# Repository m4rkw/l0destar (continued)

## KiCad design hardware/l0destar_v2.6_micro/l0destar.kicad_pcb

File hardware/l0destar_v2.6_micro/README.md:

# l0destar v2.6 micro

## Overview

- This is a prototype l0destar vehicle tracker PCB designed to be
  hand-solderable (hot air required)
- It makes use of the [Makerdiary nRF9151 Connect Kit](https://makerdiary.com/products/nrf9151-connectkit) to provide the LTE and GPS
functions
- Component vias are dogleg-routed deliberately in order to keep the PCB costs
as low as possible
- The RF trace width is calculated using a standard 4-layer stackup at JLCPCB,
  different fabrication processes may require adjustment

## Disclaimer

This is a prototype, not a product. Nothing here is validated or certified,
the parts lists are examples rather than a verified BOM, and any test results
recorded below are my own unverified bench observations - repeat the testing
yourself rather than taking them on trust.

**Before building or installing anything from this repository, read the
[full disclaimer](../../DISCLAIMER.md).**

## Test status

| Item | Test | Result | Notes |
|---------|------|--------|-------|
| Input stage | 12V input reverse polarity | PASSED | |
| Input stage | 12V ignition input reverse polarity | PASSED | |
| INA228 | Voltage reading function | PASSED |
| Ignition presence | Ignition sense 3.3v signal | PASSED | |
| LT8609 | 4.2V output | PASSED | |
| Auxillary 3.3V rail | Switches on enable signal | PASSED | |
| Accelerometer | Operates while awake | PASSED | |
| Accelerometer | Wake on motion | PASSED | |
| GPS antenna bias tee | Obtains GPS signal | PASSED | |
| Board | Quiescent current | 120 µA | |

## Features

 - 12V live and 12V ignition inputs with TVS and reverse polarity protection
 - Ignition presence sensing
 - INA228 voltage reading
 - High efficiency buck converter
 - Auxillary 3.3V rail for the GPS antenna bias tee
 - ASM330LHHXG1TR 6-axis IMU gyro/accelerometer
 - USB-C can be connected and disconnected for programming without any power
   disruption

## Changes from v2.5

 - Added stacked 47uF ceramic bulk on the 12V input to provide additional
   resilience against automotive transient spikes

## Power supply

The Connect Kit can be powered through VBUS which would be much simpler as it
can take 5V, but then you have to disconnect the power before connecting a USB
cable. Same for the Nordic dev board - they both explicitly say not to connect
powered USB and VBUS at the same time. Because the intention is to install this
in a vehicle for testing the pragmatic decision was taken to power it with a
4.2V buck feeding the battery connector. With this power connection we can
connect USB-C at any time to update the firmware without needing to disconnect
power.

## Bill of materials

| Item | Description | Specification | Example | Notes |
|------|-------------|---------------|---------|-------|
| MCU | MCU and GSM/GPS 40pin board | nRF9151 Connect Kit | [Makerdiary nRF9151 Connect Kit](https://makerdiary.com/products/nrf9151-connectkit) | |
| S1J1 | Molex Micro-fit 3.0 2x02 PCB connector | 43045-0400 | [43045-0400](https://uk.farnell.com/molex/43045-0400/conn-r-a-pcb-hdr-4pos-2row-3mm/dp/9733019) | | 
| S1J2 | Makerdiary header 1 | 20-pin 2.54mm header | [20-pin pcb header](https://amzn.to/44hTFGN) | |
| S1J3 | Makerdiary header 2 | 20-pin 2.54mm header | [20-pin pcb header](https://amzn.to/44hTFGN) | |
| S1R1 | I2C pull-up resistor | 0402 4.7K 1% | [MP003476](https://uk.farnell.com/multicomp-pro/mp003476/res-4k7-1-0-0625w-0402-thick-film/dp/3392645) | |
| S1R2 | I2C pull-up resistor | 0402 4.7K 1% | [MP003476](https://uk.farnell.com/multicomp-pro/mp003476/res-4k7-1-0-0625w-0402-thick-film/dp/3392645) | |
| S1C1 | 220uF buck output capacitor | 1210 220uF 6.3V 20% X5R | [GRM32ER60J227ME05K](https://uk.farnell.com/murata/grm32er60j227me05k/cap-220-f-6-3v-20-x5r-1210/dp/2671587) | Higher voltage/X7R spec is better if available |
| S1C2 | 220uF buck output capacitor | 1210 220uF 6.3V 20% X5R | [GRM32ER60J227ME05K](https://uk.farnell.com/murata/grm32er60j227me05k/cap-220-f-6-3v-20-x5r-1210/dp/2671587) | Higher voltage/X7R spec is better if available |
| S2Q1 | Reverse-polarity MOSFET | SQ2361 SOT-23 | [SQ2361ES-T1_GE3](https://uk.farnell.com/vishay/sq2361es-t1-ge3/mosfet-aec-q101-p-ch-60v-sot-23/dp/2889711) | |
| S2Q2 | Reverse-polarity MOSFET | SQ2361 SOT-23 | [SQ2361ES-T1_GE3](https://uk.farnell.com/vishay/sq2361es-t1-ge3/mosfet-aec-q101-p-ch-60v-sot-23/dp/2889711) | |
| S2D1 | 15V Zener diode | BZX84C15 | [BZX84C15](https://uk.farnell.com/multicomp-pro/bzx84c15/zener-diode-0-3w-15v-sot-23/dp/2675186) | |
| S2D2 | 400W TVS diode | PTVS33VS1UTR,115 SOD-123W | [PTVS33VS1UTR,115](https://uk.farnell.com/nexperia/ptvs33vs1utr-115/tvs-diode-aecq101-unidir-33v-400w/dp/3440137) | |
| S2D3 | 15V Zener diode | BZX84C15 | [BZX84C15](https://uk.farnell.com/multicomp-pro/bzx84c15/zener-diode-0-3w-15v-sot-23/dp/2675186) | |
| S2D4 | 400W TVS diode | PTVS33VS1UTR,115 SOD-123W | [PTVS33VS1UTR,115](https://uk.farnell.com/nexperia/ptvs33vs1utr-115/tvs-diode-aecq101-unidir-33v-400w/dp/3440137) | |
| S2R1 | Pulldown resistor | 0402 1% 1M | [ERJ2RKF1004X](https://uk.farnell.com/panasonic/erj2rkf1004x/res-1m-1-0-1w-0402-thick-film/dp/2302957) | |
| S2R2 | Pulldown resistor | 0402 1% 1M | [ERJ2RKF1004X](https://uk.farnell.com/panasonic/erj2rkf1004x/res-1m-1-0-1w-0402-thick-film/dp/2302957) | |
| S2C1 | 47uF input capacitor | 2220 >= 50V 20% X7R | [CKG57NX7R1H476M500JH](https://uk.farnell.com/tdk/ckg57nx7r1h476m500jh/cap-stacked-47uf-50v-mlcc-2220/dp/3816888) | |
| S3U1 | INA228 voltage read IC | INA228 10-VSSOP | [INA228](https://www.aliexpress.com/item/1005008704299153.html) | |
| S3C1 | 1uF capacitor | 0402 >= 10V 10% X7R | [KAM05CR71A105KH](https://uk.farnell.com/kyocera-avx/kam05cr71a105kh/capacitor-mlcc-1uf-x7r-10v-0402/dp/4365709) | |
| S3C2 | 100nF capacitor | 0402 >= 25V 10% X7R | [MC0402B104K250CT](https://uk.farnell.com/multicomp-pro/mc0402b104k250ct/cap-0-1-f-25v-10-x7r-0402/dp/2320759) | |
| S4Q1 | Ignition sense MOSFET | 2N7002 SOT-23 | [2N7002](https://uk.farnell.com/multicomp-pro/2n7002/mosfet-n-ch-60v-0-115a-sot-23/dp/4295174) | |
| S4R1 | Ignition sense resistor | 0402 120K 1% | [RC0402FR-07120KL](https://uk.farnell.com/yageo/rc0402fr-07120kl/res-120k-1-0-063w-0402-thick-film/dp/9239480) | |
| S4R2 | Ignition sense resistor | 0402 47K 1% | [ERJ2RKF4702X](https://uk.farnell.com/panasonic/erj2rkf4702x/res-47k-1-0-1w-0402-thick-film/dp/2302806) | |
| S4R3 | Ignition sense resistor | 0402 56K 1% | [MCMR04X5602FTL](https://uk.farnell.com/multicomp-pro/mcmr04x5602ftl/res-56k-1-0-0625w-0402-ceramic/dp/2073131) | |
| S4C1 | 100nF capacitor | 0402 >= 25V 10% X7R | [MC0402B104K250CT](https://uk.farnell.com/multicomp-pro/mc0402b104k250ct/cap-0-1-f-25v-10-x7r-0402/dp/2320759) | |
| S6U1 | Buck converter | LT8609AIMSE MSOP-EP-10 | [LT8609AIMSE#PBF](https://uk.farnell.com/analog-devices/lt8609aimse-pbf/dc-dc-conv-sync-buck-2mhz-125deg/dp/4025049) | |
| S6U2 | Ideal diode | LM66100 | [LM66100](https://www.aliexpress.com/item/1005008565117953.html) | |
| S6L1 | Inductor | XFL4020-222ME | [XFL4020-222MEC](https://uk.farnell.com/coilcraft/xfl4020-222mec/inductor-2-2uh-8a-20-pwr-38mhz/dp/2289216) | |
| S6C1 | 100nF capacitor | 0402 >= 25V 10% X7R | [MC0402B104K250CT](https://uk.farnell.com/multicomp-pro/mc0402b104k250ct/cap-0-1-f-25v-10-x7r-0402/dp/2320759) | |
| S6C2 | 1uF capacitor | 0402 >= 10V 10% X7R | [KAM05CR71A105KH](https://uk.farnell.com/kyocera-avx/kam05cr71a105kh/capacitor-mlcc-1uf-x7r-10v-0402/dp/4365709) | |
| S6C3 | 4.7uF capacitor | 0805 >= 50V 10% X7R | [GRM21BZ71H475KE15K](https://uk.farnell.com/murata/grm21bz71h475ke15k/cap-4-7uf-50v-mlcc-0805/dp/3582887) | |
| S6C4 | 10pF capacitor | 0402 >= 25V 10% X7R | [C0402C100K5RACTU](https://uk.farnell.com/kemet/c0402c100k5ractu/cap-10pf-50v-10-x7r-0402/dp/2821254) | |
| S6C5 | 22uF capacitor | 0805 >= 10V 20% X7T | [GCM21BD71A226MEC4L](https://uk.farnell.com/murata/gcm21bd71a226mec4l/cap-mlcc-22uf-x7t-10v-0805/dp/4813843) | Higher voltage rating/X7R is better if available |
| S6R1 | Oscillator frequency resistor | 0402 18.2K 1% | [RC0402FR-0718K2L](https://uk.farnell.com/yageo/rc0402fr-0718k2l/res-18k2-1-0-0625w-0402-thick/dp/3495542) | 18.2K == 2MHz |
| S6R2 | Output voltage divider resistor | 0402 226K 1% | [MCMR04X2263FTL](https://uk.farnell.com/multicomp-pro/mcmr04x2263ftl/res-226k-1-0-0625w-0402-ceramic/dp/2072796) | VOUT == 0.782V x (1 + S6R3/S6R2) == 4.24V |
| S6R3 | Output voltage divider resistor | 0402 1M 1% | [ERJ2RKF1004X](https://uk.farnell.com/panasonic/erj2rkf1004x/res-1m-1-0-1w-0402-thick-film/dp/2302957) | VOUT == 0.782V x (1 + S6R3/S6R2) == 4.24V |
| S7Q1 | Aux power MOSFET | 2N7002 SOT-23 | [2N7002](https://uk.farnell.com/multicomp-pro/2n7002/mosfet-n-ch-60v-0-115a-sot-23/dp/4295174) | |
| S7Q2 | Aux power MOSFET | DMG3415U SOT-23 | [DMG3415UQ-7](https://uk.farnell.com/diodes-inc/dmg3415uq-7/mosfet-p-ch-20v-4a-sot-23/dp/3943490) | |
| S7R1 | Aux power resistor | 0402 100K 1% | [MCPWR02FTEP1003A](https://uk.farnell.com/multicomp-pro/mcpwr02ftep1003a/res-100k-1-thick-film-0402/dp/4538624) | |
| S7R2 | Aux power resistor | 0402 1M 1% | [ERJ2RKF1004X](https://uk.farnell.com/panasonic/erj2rkf1004x/res-1m-1-0-1w-0402-thick-film/dp/2302957) | |
| S7R3 | Aux power resistor | 0402 100K 1% | [MCPWR02FTEP1003A](https://uk.farnell.com/multicomp-pro/mcpwr02ftep1003a/res-100k-1-thick-film-0402/dp/4538624) | |
| S7R4 | Aux power resistor | 0402 470K 1% | [ERJ2RKF4703X](https://uk.farnell.com/panasonic/erj2rkf4703x/res-470k-1-0-1w-0402-thick-film/dp/2302916) | |
| S8U1 | ASM330LHHXTR accelerometer | ASM330LHHXTR | [ASM330LHHXTR](https://estore.st.com/en/products/mems-and-sensors/inemo-inertial-modules/asm330lhhx.html) | |
| S8C1 | 100nF capacitor | 0402 >= 25V 10% X7R | [MC0402B104K250CT](https://uk.farnell.com/multicomp-pro/mc0402b104k250ct/cap-0-1-f-25v-10-x7r-0402/dp/2320759) | |
| S8C2 | 10uF capacitor | 0603 >= 6.3V 20% X7T | [GRT188D71A106ME13D](https://uk.farnell.com/murata/grt188d71a106me13d/cap-mlcc-10uf-x7t-10v-0603/dp/4335734) | Higher voltage/X7R is better if available |
| S8C3 | 100nF capacitor | 0402 >= 25V 10% X7R | [MC0402B104K250CT](https://uk.farnell.com/multicomp-pro/mc0402b104k250ct/cap-0-1-f-25v-10-x7r-0402/dp/2320759) | |
| S13R1 | LED resistor | 0402 1K 1% | [CRCW04021K00FKED](https://uk.farnell.com/vishay/crcw04021k00fked/res-1k-1-0-063w-0402-thick-film/dp/1469662) | |
| S13R2 | LED resistor | 0402 1K 1% | [CRCW04021K00FKED](https://uk.farnell.com/vishay/crcw04021k00fked/res-1k-1-0-063w-0402-thick-film/dp/1469662) | |
| S13R3 | LED resistor | 0402 1K 1% | [CRCW04021K00FKED](https://uk.farnell.com/vishay/crcw04021k00fked/res-1k-1-0-063w-0402-thick-film/dp/1469662) | |
| S13D1 | Status LED | 0603 | [MP001249](https://uk.farnell.com/multicomp-pro/mp001249/led-red-385mcd-629nm-0603/dp/3265380) | |
| S13D2 | Status LED | 0603 | [MP001249](https://uk.farnell.com/multicomp-pro/mp001249/led-red-385mcd-629nm-0603/dp/3265380) | |
| S13D3 | Status LED | 0603 | [MP001249](https://uk.farnell.com/multicomp-pro/mp001249/led-red-385mcd-629nm-0603/dp/3265380) | |
| S15J1 | u.FL PCB connector | 50 ohm | [U.FL-R-SMT(01)](https://uk.farnell.com/hirose-hrs/u-fl-r-smt-01/rf-coaxial-u-fl-straight-jack/dp/3908021) | |
| S15J2 | SMA PCB connector | 50 ohm | [SMA-J-P-H-RA-TH1](https://uk.farnell.com/samtec/sma-j-p-h-ra-th1/rf-coaxial-sma-jack-50-ohm-pcb/dp/2856817) | |
| S15J3 | u.FL PCB connector | 50 ohm | [U.FL-R-SMT(01)](https://uk.farnell.com/hirose-hrs/u-fl-r-smt-01/rf-coaxial-u-fl-straight-jack/dp/3908021) | |
| S15J4 | SMA PCB connector | 50 ohm | [SMA-J-P-H-RA-TH1](https://uk.farnell.com/samtec/sma-j-p-h-ra-th1/rf-coaxial-sma-jack-50-ohm-pcb/dp/2856817) | |
| S15U1 | Ideal diode | LM66100 | [LM66100](https://www.aliexpress.com/item/1005008565117953.html) | |
| S15FB1 | Ferrite bead | 600 ohm | [BLM15PX601SZ1D](https://uk.farnell.com/murata/blm15px601sz1d/ferrite-bead-0-9a-0-23ohm-0402/dp/3678458) | |
| S15L1 | RF inductor | 0603 47-100 nH, SRF > 2GHz | [LQW18AN68NJ00D](https://uk.farnell.com/murata/lqw18an68nj00d/inductor-68nh-2-2ghz-0-34a-0603/dp/3471533) | |
| S15C1 | 100pF RF capacitor | 0402 >= 25V 1% C0G / NP0 | [AC0402FRNPO9BN101](https://uk.farnell.com/yageo/ac0402frnpo9bn101/cap-100pf-50v-mlcc-0402/dp/4166091) | |
| S15C2 | 100pF RF capacitor | 0402 >= 25V 1% C0G / NP0 | [AC0402FRNPO9BN101](https://uk.farnell.com/yageo/ac0402frnpo9bn101/cap-100pf-50v-mlcc-0402/dp/4166091) | |
| S15C3 | 10nF RF capacitor | 0402 >= 25V 5% C0G / NP0 | [GRM1555CYA103JE01D](https://uk.farnell.com/murata/grm1555cya103je01d/cap-mlcc-0-01uf-c0g-np0-35v-0402/dp/4792250) | |
| S15C4 | 1uF RF capacitor | 0402 >= 25V 10% X7R | [KAM05CR71A105KH](https://uk.farnell.com/kyocera-avx/kam05cr71a105kh/capacitor-mlcc-1uf-x7r-10v-0402/dp/4365709) | |
| - | u.FL cable - LTE | 50 ohm 35mm | [U.FL-2LPHF6-04N1TV-A-35](https://uk.farnell.com/hirose-hrs/u-fl-2lphf6-04n1tv-a-35/cbl-assy-u-fl-r-a-plug-r-a-plug/dp/4294251) | |
| - | u.FL cable - GPS | 50 ohm 35mm | [U.FL-2LPHF6-04N1TV-A-35](https://uk.farnell.com/hirose-hrs/u-fl-2lphf6-04n1tv-a-35/cbl-assy-u-fl-r-a-plug-r-a-plug/dp/4294251) | |
| - | JST power cable | Ultra-thin MX1.25 51146 | [10PCS MX1.25 51146 Cable](https://www.aliexpress.com/item/4000586964114.html) | |

## Parts list

| Item | Quantity | Specification | Example | Notes |
|------|----------|---------------|---------|-------|
| MCU and GSM/GPS 40pin board | 1 | nRF9151 Connect Kit | [Makerdiary nRF9151 Connect Kit](https://makerdiary.com/products/nrf9151-connectkit) | |
| Molex Micro-fit 3.0 2x02 PCB connector | 1 | 43045-0400 | [43045-0400](https://uk.farnell.com/molex/43045-0400/conn-r-a-pcb-hdr-4pos-2row-3mm/dp/9733019) | | 
| 20pin header | 2 | 20-pin 2.54mm header | [20-pin pcb header](https://amzn.to/44hTFGN) | |
| 1K 0402 resistor | 3 | 0402 1K 1% | [CRCW04021K00FKED](https://uk.farnell.com/vishay/crcw04021k00fked/res-1k-1-0-063w-0402-thick-film/dp/1469662) | |
| 4.7K 0402 resistor | 2 | 0402 4.7K 1% | [MP003476](https://uk.farnell.com/multicomp-pro/mp003476/res-4k7-1-0-0625w-0402-thick-film/dp/3392645) | |
| 18.2K 0402 resistor | 1 | 0402 18.2K 1% | [RC0402FR-0718K2L](https://uk.farnell.com/yageo/rc0402fr-0718k2l/res-18k2-1-0-0625w-0402-thick/dp/3495542) | 18.2K == 2MHz |
| 47K 0402 resistor | 1 | 0402 47K 1% | [ERJ2RKF4702X](https://uk.farnell.com/panasonic/erj2rkf4702x/res-47k-1-0-1w-0402-thick-film/dp/2302806) | |
| 56K 0402 resistor | 1 | 0402 56K 1% | [MCMR04X5602FTL](https://uk.farnell.com/multicomp-pro/mcmr04x5602ftl/res-56k-1-0-0625w-0402-ceramic/dp/2073131) | |
| 100K 0402 resistor | 2 | 0402 100K 1% | [MCPWR02FTEP1003A](https://uk.farnell.com/multicomp-pro/mcpwr02ftep1003a/res-100k-1-thick-film-0402/dp/4538624) | |
| 120K 0402 resistor | 1 | 0402 120K 1% | [RC0402FR-07120KL](https://uk.farnell.com/yageo/rc0402fr-07120kl/res-120k-1-0-063w-0402-thick-film/dp/9239480) | |
| 226K 0402 resistor | 1 | 0402 226K 1% | [MCMR04X2263FTL](https://uk.farnell.com/multicomp-pro/mcmr04x2263ftl/res-226k-1-0-0625w-0402-ceramic/dp/2072796) | VOUT == 0.782V x (1 + S6R3/S6R2) == 4.24V |
| 470K 0402 resistor | 1 | 0402 470K 1% | [ERJ2RKF4703X](https://uk.farnell.com/panasonic/erj2rkf4703x/res-470k-1-0-1w-0402-thick-film/dp/2302916) | |
| 1M 0402 resistor | 4 | 0402 1M 1% | [ERJ2RKF1004X](https://uk.farnell.com/panasonic/erj2rkf1004x/res-1m-1-0-1w-0402-thick-film/dp/2302957) | |
| 10pF 0402 capacitor | 1 | 0402 >= 25V 10% X7R | [C0402C100K5RACTU](https://uk.farnell.com/kemet/c0402c100k5ractu/cap-10pf-50v-10-x7r-0402/dp/2821254) | |
| 100pF 0402 RF capacitor | 2 | 0402 >= 25V 1% C0G / NP0 | [AC0402FRNPO9BN101](https://uk.farnell.com/yageo/ac0402frnpo9bn101/cap-100pf-50v-mlcc-0402/dp/4166091) | |
| 10nF 0402 RF capacitor | 1 | 0402 >= 25V 5% C0G / NP0 | [GRM1555CYA103JE01D](https://uk.farnell.com/murata/grm1555cya103je01d/cap-mlcc-0-01uf-c0g-np0-35v-0402/dp/4792250) | |
| 100nF 0402 capacitor | 5 | 0402 >= 25V 10% X7R | [MC0402B104K250CT](https://uk.farnell.com/multicomp-pro/mc0402b104k250ct/cap-0-1-f-25v-10-x7r-0402/dp/2320759) | |
| 1uF 0402 capacitor | 3 | 0402 >= 10V 10% X7R | [KAM05CR71A105KH](https://uk.farnell.com/kyocera-avx/kam05cr71a105kh/capacitor-mlcc-1uf-x7r-10v-0402/dp/4365709) | |
| 4.7uF 0805 capacitor | 1 | 0805 >= 50V 10% X7R | [GRM21BZ71H475KE15K](https://uk.farnell.com/murata/grm21bz71h475ke15k/cap-4-7uf-50v-mlcc-0805/dp/3582887) | |
| 10uF 0603 capacitor | 1 | 0603 >= 6.3V 20% X7T | [GRT188D71A106ME13D](https://uk.farnell.com/murata/grt188d71a106me13d/cap-mlcc-10uf-x7t-10v-0603/dp/4335734) | Higher voltage/X7R is better if available |
| 22uF 0805 capacitor | 1 | 0805 >= 10V 20% X7T | [GCM21BD71A226MEC4L](https://uk.farnell.com/murata/gcm21bd71a226mec4l/cap-mlcc-22uf-x7t-10v-0805/dp/4813843) | Higher voltage rating/X7R is better if available |
| 47uF 2220 capacitor | 1 | 2220 >= 50V 20% X7R | [CKG57NX7R1H476M500JH](https://uk.farnell.com/tdk/ckg57nx7r1h476m500jh/cap-stacked-47uf-50v-mlcc-2220/dp/3816888) | |
| 220uF 1210 capacitor | 2 | 1210 6.3V 20% X5R | [GRM32ER60J227ME05K](https://uk.farnell.com/murata/grm32er60j227me05k/cap-220-f-6-3v-20-x5r-1210/dp/2671587) | Higher voltage/X7R spec is better if available |
| MOSFET | 2 | SQ2361 SOT-23 | [SQ2361ES-T1_GE3](https://uk.farnell.com/vishay/sq2361es-t1-ge3/mosfet-aec-q101-p-ch-60v-sot-23/dp/2889711) | |
| MOSFET | 2 | 2N7002 SOT-23 | [2N7002](https://uk.farnell.com/multicomp-pro/2n7002/mosfet-n-ch-60v-0-115a-sot-23/dp/4295174) | |
| MOSFET | 1 | DMG3415U SOT-23 | [DMG3415UQ-7](https://uk.farnell.com/diodes-inc/dmg3415uq-7/mosfet-p-ch-20v-4a-sot-23/dp/3943490) | |
| 15V Zener diode | 2 | BZX84C15 | [BZX84C15](https://uk.farnell.com/multicomp-pro/bzx84c15/zener-diode-0-3w-15v-sot-23/dp/2675186) | |
| 400W TVS diode | 2 | PTVS33VS1UTR,115 SOD-123W | [PTVS33VS1UTR,115](https://uk.farnell.com/nexperia/ptvs33vs1utr-115/tvs-diode-aecq101-unidir-33v-400w/dp/3440137) | |
| Ideal diode | 2 | LM66100 | [LM66100](https://www.aliexpress.com/item/1005008565117953.html) | |
| INA228 voltage read IC | 1 | INA228 10-VSSOP | [INA228](https://www.aliexpress.com/item/1005008704299153.html) | |
| Buck converter | 1 | LT8609AIMSE MSOP-EP-10 | [LT8609AIMSE#PBF](https://uk.farnell.com/analog-devices/lt8609aimse-pbf/dc-dc-conv-sync-buck-2mhz-125deg/dp/4025049) | |
| Inductor | 1 | XFL4020-222ME | [XFL4020-222MEC](https://uk.farnell.com/coilcraft/xfl4020-222mec/inductor-2-2uh-8a-20-pwr-38mhz/dp/2289216) | |
| ASM330LHHXTR accelerometer | 1 | ASM330LHHXTR | [ASM330LHHXTR](https://estore.st.com/en/products/mems-and-sensors/inemo-inertial-modules/asm330lhhx.html) | |
| 0603 LED | 3 | 0603 | [MP001249](https://uk.farnell.com/multicomp-pro/mp001249/led-red-385mcd-629nm-0603/dp/3265380) | |
| Ferrite bead | 1 | 600 ohm | [BLM15PX601SZ1D](https://uk.farnell.com/murata/blm15px601sz1d/ferrite-bead-0-9a-0-23ohm-0402/dp/3678458) | |
| RF inductor | 1 | 0603 47-100 nH, SRF > 2GHz | [LQW18AN68NJ00D](https://uk.farnell.com/murata/lqw18an68nj00d/inductor-68nh-2-2ghz-0-34a-0603/dp/3471533) | |
| u.FL PCB connector | 2 | 50 ohm | [U.FL-R-SMT(01)](https://uk.farnell.com/hirose-hrs/u-fl-r-smt-01/rf-coaxial-u-fl-straight-jack/dp/3908021) | |
| SMA PCB connector | 2 | 50 ohm | [SMA-J-P-H-RA-TH1](https://uk.farnell.com/samtec/sma-j-p-h-ra-th1/rf-coaxial-sma-jack-50-ohm-pcb/dp/2856817) | |
| u.FL cable - GPS | 2 | 50 ohm 35mm | [U.FL-2LPHF6-04N1TV-A-35](https://uk.farnell.com/hirose-hrs/u-fl-2lphf6-04n1tv-a-35/cbl-assy-u-fl-r-a-plug-r-a-plug/dp/4294251) | |
| JST power cable | 1 | Ultra-thin MX1.25 51146 | [10PCS MX1.25 51146 Cable](https://www.aliexpress.com/item/4000586964114.html) | |

## Images

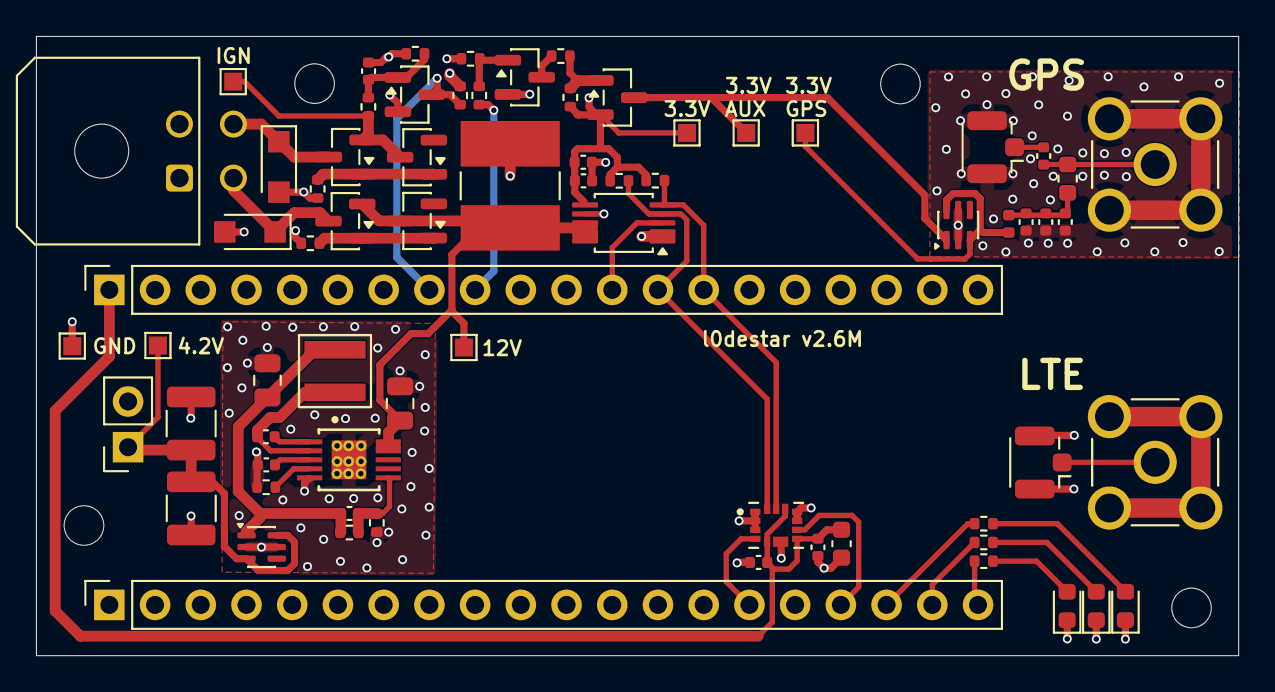
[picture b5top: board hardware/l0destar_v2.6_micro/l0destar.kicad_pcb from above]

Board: 4 copper layers, 66.8 x 34.4 mm, 74 parts (0 on the bottom side), 38 nets.

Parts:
GND1: TestPoint; TestPoint_Pad_1.0x1.0mm
H1, H2, H3, H4: MountingHole; MountingHole_2.2mm_M2
PP3V3, PP3V3AUX1, PP3V3GPS2, PP4V5, PP12VIP1, PP12VP1: TestPoint; TestPoint_Pad_1.0x1.0mm
S1C1, S1C2: 220uF; C_1210_3225Metric
S1J1: Main connector; Molex_Micro-Fit_3.0_43045-0400_2x02_P3.00mm_Horizontal
S1J2: Conn_01x20_Socket; MakerDiary_nRF9151_ConnectKit_PinHeader_1-20
S1J3: Conn_01x20_Socket_21-40; MakerDiary_nRF9151_ConnectKit_PinHeader_21-40
S1J4: VCC; PinSocket_1x02_P2.54mm_Vertical
S1R1, S1R2: 4.7K; R_0402_1005Metric
S2C1: CKG57NX7R1H476M500JH 47uF; CAPC6050X550N
S2D1, S2D3: BZX84C15; SOT-23
S2D2, S2D4: PTVS33VS1UTR,115; Nexperia_CFP3_SOD-123W
S2Q1, S2Q2: SQ2361; SOT-23
S2R1, S2R2, S6R3, S7R2: 1M; R_0402_1005Metric
S3C1, S6C2, S15C4: 1uF; C_0402_1005Metric
S3C2, S4C1, S6C1, S8C1, S8C3: 100nF; C_0402_1005Metric
S3U1: INA228; TSSOP-10_3x3mm_P0.5mm
S4Q1, S7Q1: 2N7002; SOT-23
S4R1: 120K; R_0402_1005Metric
S4R2: 47K; R_0402_1005Metric
S4R3: 56K; R_0402_1005Metric
S6C3: 4.7uF; C_0805_2012Metric
S6C4: 10pF; C_0402_1005Metric
S6C5: 22uF; C_0805_2012Metric
S6L1: XFL4020-222ME; IND_XFL4020-222ME
S6R1: 18.2K; R_0402_1005Metric
S6R2: 226K; R_0402_1005Metric
S6U1: LT8609AIMSE_PBF; LT8609AIMSE_WITH_GROUND_VIAS
S6U2, S15U1: LM66100DCK; SOT-363_SC-70-6
S7Q2: DMG3415U; SOT-23
S7R1, S7R3: 100K; R_0402_1005Metric
S7R4: 470K; R_0402_1005Metric
S8C2: 10uF; C_0603_1608Metric
S8U1: ASM330LHHXTR; XDCR_ASM330LHHXTR
S13D1, S13D2, S13D3: LED; LED_0603_1608Metric
S13R1, S13R2, S13R3: 1K; R_0402_1005Metric
S15C1, S15C2: 100pF; C_0402_1005Metric
S15C3: 10nF; C_0402_1005Metric
S15FB1: 600R; L_0402_1005Metric
S15J1: GPS_UFL; U.FL_Hirose_U.FL-R-SMT-1_Vertical
S15J2: GPS_SMA; SAMTEC_SMA-J-P-H-RA-TH1
S15J3: GSM_UFL; U.FL_Hirose_U.FL-R-SMT-1_Vertical
S15J4: GSM_SMA; SAMTEC_SMA-J-P-H-RA-TH1
S15L1: 47-100 nH, SRF > 2 GHz; L_0603_1608Metric

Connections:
ACCELL_INT1: S1J2.15, S8U1.4 (INT1)
ACCELL_INT2: S1J2.17, S8U1.9 (INT2)
AUX_ENABLE: S1J3.32 (Pin_9), S7R1.1
GND: GND1.1 (1_1), S1C1.2, S1C2.2, S1J1.1, S1J2.3 (GND), S1J3.39 (Pin_2), S1J4.2, S2C1.2, S2D2.2 (A), S2D4.2 (A), S2R1.2, S2R2.2, S3C1.1, S3C2.1, S3U1.1 (A1), S3U1.2 (A0), S3U1.7 (GND), S4C1.2, S4Q1.2 (S), S4R2.1, S6C2.2, S6C3.2, S6C5.2, S6R1.2, S6R2.2, S6U1.5 (SYNC), S6U1.11 (GND), S6U2.2 (GND), S6U2.5 (ST), S7Q1.2 (S), S7R2.1, S8C1.2, S8C2.2, S8C3.2, S8U1.1 (SDO/SA0), S8U1.2 (MSDA), S8U1.3 (MSCL), S8U1.6 (NC), S8U1.7 (GND), S8U1.10 (NC), S8U1.11 (NC), S13D1.1 (K), S13D2.1 (K), S13D3.1 (K), S15C2.2, S15C3.2, S15C4.2, S15J1.2 (Ext), S15J2.2, S15J2.3, S15J2.4, S15J2.5, S15J3.2 (Ext), S15J4.2, S15J4.3, S15J4.4, S15J4.5, S15U1.2 (GND), S15U1.5 (ST)
I2C_SCL: S1J3.27 (Pin_14), S1R2.1, S3U1.5 (SCL), S8U1.13 (SCL)
I2C_SDA: S1J3.28 (Pin_13), S1R1.1, S3U1.4 (SDA), S8U1.14 (SDA)
IGN_SENSE: S1J3.33 (Pin_8), S4Q1.3 (D), S4R3.2
INA_ALRT: S1J3.29 (Pin_12), S3U1.3 (~Alert)
LED1: S1J2.20, S13R1.2
LED2: S1J2.19, S13R2.2
LED3: S1J2.18, S13R3.2
unnamed: S2D1.1 (A), S2Q1.1 (G), S2R1.1
unnamed: S2D3.1 (A), S2Q2.1 (G), S2R2.1
unnamed: S4C1.1, S4Q1.1 (G), S4R1.2, S4R2.2
unnamed: S6C1.1, S6U1.1 (BST)
unnamed: S6C4.1, S6R2.1, S6R3.1, S6U1.6 (FB)
unnamed: S6C2.1, S6U1.3 (INTVCC)
unnamed: S6R1.1, S6U1.4 (RT)
unnamed: S6C1.2, S6L1.1, S6U1.2 (SW)
unnamed: S6C4.2, S6C5.1, S6L1.2, S6R3.2, S6U2.1 (VIN)
unnamed: S7Q1.3 (D), S7R3.2
unnamed: S7Q1.1 (G), S7R1.2, S7R2.2
unnamed: S7Q2.1 (G), S7R3.1, S7R4.2
unnamed: S13D1.2 (A), S13R1.1
unnamed: S13D2.2 (A), S13R2.1
unnamed: S13D3.2 (A), S13R3.1
unnamed: S15C2.1, S15C3.1, S15C4.1, S15FB1.2, S15L1.1
unnamed: S15C1.1, S15J1.1 (In)
unnamed: S15J3.1 (In), S15J4.1
PP3V3: PP3V3.1 (1_1), S1J3.40 (Pin_1), S1R1.2, S1R2.2, S3C1.2, S3C2.2, S3U1.6 (VS), S4R3.1, S7Q2.2 (S), S7R4.1, S8C1.1, S8C2.1, S8C3.1, S8U1.5 (VDD_IO), S8U1.8 (VDD), S8U1.12 (CS)
PP3V3_AUX: PP3V3AUX1.1 (1_1), S7Q2.3 (D), S15U1.1 (VIN)
PP3V3_GPS: PP3V3GPS2.1 (1_1), S15FB1.1, S15U1.3 (~CE), S15U1.6 (VOUT)
PP4V2: PP4V5.1 (1_1), S1C1.1, S1C2.1, S1J4.1, S6U2.3 (~CE), S6U2.6 (VOUT)
PP12V: S1J1.3, S2D4.1 (K), S2Q2.3 (D)
PP12VI: S1J1.4, S2D2.1 (K), S2Q1.3 (D)
PP12VIP: PP12VIP1.1 (1_1), S2D1.3 (K), S2Q1.2 (S), S4R1.1
PP12VP: PP12VP1.1 (1_1), S2C1.1, S2D3.3 (K), S2Q2.2 (S), S3U1.8 (Vbus), S3U1.9 (Vin-), S3U1.10 (Vin+), S6C3.1, S6U1.9 (VIN), S6U1.10 (EN/UV)
RF: S15C1.2, S15J2.1, S15L1.2

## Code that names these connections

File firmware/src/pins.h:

#ifndef PINS_H_
#define PINS_H_

/* PCB pin assignments — P0.x GPIO numbers, -1 = not fitted on this board.
 *
 * All values come from Kconfig (APP_PIN_*).  The per-board defaults live in
 * Kconfig.boards, selected by the APP_BOARD choice; a bench or board variant
 * can still remap any signal from local.conf without touching code. */
#define PIN_K1_TX      CONFIG_APP_PIN_K1_TX
#define PIN_K1_RX      CONFIG_APP_PIN_K1_RX
#define PIN_K2_TX      CONFIG_APP_PIN_K2_TX
#define PIN_K2_RX      CONFIG_APP_PIN_K2_RX
#define PIN_L_SEND     CONFIG_APP_PIN_L_SEND
#define PIN_L_RECV     CONFIG_APP_PIN_L_RECV
#define PIN_L_SENSE    CONFIG_APP_PIN_L_SENSE
#define PIN_K_EN       CONFIG_APP_PIN_K_EN
#define PIN_K_SLEEP    CONFIG_APP_PIN_K_SLEEP
#define PIN_AUX_SW     CONFIG_APP_PIN_AUX_SW
#define PIN_OBD_EN     CONFIG_APP_PIN_OBD_EN
#define PIN_CAN_EN     CONFIG_APP_PIN_CAN_EN
#define PIN_TWI_SDA    CONFIG_APP_PIN_TWI_SDA
#define PIN_TWI_SCL    CONFIG_APP_PIN_TWI_SCL
#define PIN_INA_ALRT   CONFIG_APP_PIN_INA_ALRT
#define PIN_ACC_INT1   CONFIG_APP_PIN_ACC_INT1
#define PIN_ACC_INT2   CONFIG_APP_PIN_ACC_INT2
#define PIN_IGN_SENSE  CONFIG_APP_PIN_IGN_SENSE

/* MCP2518FD CAN controller (SPI bit-banged; -1 on boards without CAN) */
#define PIN_CAN_SCK    CONFIG_APP_PIN_CAN_SCK
#define PIN_CAN_SDI    CONFIG_APP_PIN_CAN_SDI
#define PIN_CAN_SDO    CONFIG_APP_PIN_CAN_SDO
#define PIN_CAN_CS     CONFIG_APP_PIN_CAN_CS
#define PIN_CAN_INT    CONFIG_APP_PIN_CAN_INT

/* Status LEDs (-1 = not fitted; LED4/5 exist only on v2.1 mini) */
#define PIN_LED1       CONFIG_APP_PIN_LED1
#define PIN_LED2       CONFIG_APP_PIN_LED2
#define PIN_LED3       CONFIG_APP_PIN_LED3
#define PIN_LED4       CONFIG_APP_PIN_LED4
#define PIN_LED5       CONFIG_APP_PIN_LED5

/* Switched-rail status sense inputs (v3.1+).  The 3.3V senses read high
 * while their rail is up; the 12V sense is inverted by a 2N7002 and reads
 * low while PP12V_K is up (CONFIG_APP_BOARD_RAIL_ST_12V_ACTIVE_LOW). */
#define PIN_GPS_RAIL_ST    CONFIG_APP_PIN_GPS_RAIL_ST
#define PIN_CAN_RAIL_ST    CONFIG_APP_PIN_CAN_RAIL_ST
#define PIN_K3V3_RAIL_ST   CONFIG_APP_PIN_K3V3_RAIL_ST
#define PIN_K12V_RAIL_ST   CONFIG_APP_PIN_K12V_RAIL_ST

/* The AUX domain's rail, as the schematic names it: the GPS antenna bias on
 * boards with the built-in receiver, the whole external receiver on v4.0. */
#ifdef CONFIG_APP_BOARD_HAS_EXT_GNSS
#define GPS_RAIL_NAME  "PP3V3_GNSS"
#else
#define GPS_RAIL_NAME  "PP3V3_GPS"
#endif

/* External GNSS receiver (v4.0): the UART to the MAX-M10S, its 1PPS output
 * and the switch for its backup supply.  -1 where there is none. */
#define PIN_GNSS_TX        CONFIG_APP_PIN_GNSS_TX
#define PIN_GNSS_RX        CONFIG_APP_PIN_GNSS_RX
#define PIN_GNSS_TIMEPULSE CONFIG_APP_PIN_GNSS_TIMEPULSE
#define PIN_GNSS_BCKP_EN   CONFIG_APP_PIN_GNSS_BCKP_EN

/* External SPI NOR flash (MX25R6435F, src/extflash.c), bit-banged.  -1 where
 * there is none.  Named as the flash sees them, like the CAN controller's:
 * SDI is data into the flash.  On the v4.1.x designs they are the CAN
 * controller's bus pins, and only FLASH_CS is its own. */
#define PIN_FLASH_SCK  CONFIG_APP_PIN_FLASH_SCK
#define PIN_FLASH_SDI  CONFIG_APP_PIN_FLASH_SDI
#define PIN_FLASH_SDO  CONFIG_APP_PIN_FLASH_SDO
#define PIN_FLASH_CS   CONFIG_APP_PIN_FLASH_CS

/* 0-30V AIO inputs (v2.1 only) */
#define PIN_AIO1       CONFIG_APP_PIN_AIO1
#define PIN_AIO2       CONFIG_APP_PIN_AIO2
#define PIN_AIO3       CONFIG_APP_PIN_AIO3
#define PIN_AIO4       CONFIG_APP_PIN_AIO4
#define PIN_AIO5       CONFIG_APP_PIN_AIO5
#define PIN_AIO6       CONFIG_APP_PIN_AIO6

/* INA and accelerometer share the TWIM bus */
#define PIN_INA_SDA    PIN_TWI_SDA
#define PIN_INA_SCL    PIN_TWI_SCL
#define PIN_ACC_SDA    PIN_TWI_SDA
#define PIN_ACC_SCL    PIN_TWI_SCL

#endif

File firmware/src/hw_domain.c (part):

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 * TJA1027T through their clamp diodes — exactly what the parking rules above
 * exist to prevent.
 *
 * A domain with no signal pins (v3.x AUX: GPS_ENABLE gates only the antenna
 * bias tee) has nothing to protect, so a rail that fails to report up is
 * treated differently: the fault is logged and alerted, but the enable is
 * left asserted and the domain counted as on.  Dropping it would only
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
static void bckp_set(bool on)
{
	if (!IS_ENABLED(CONFIG_APP_GNSS_BACKUP_SUPPLY) || PIN_GNSS_BCKP_EN < 0 ||
	    on == s_bckp_on) {
		return;
	}
	gpio_pin_configure(hw_gpio0, PIN_GNSS_BCKP_EN,
			   on ? GPIO_OUTPUT_HIGH : GPIO_OUTPUT_LOW);
	s_bckp_on = on;
	bklog_note(on);
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
static void dom_add_can_pins(struct domain *d)
{
	dom_add(d, PIN_CAN_SCK, ROLE_OUT_LOW);
	dom_add(d, PIN_CAN_SDI, ROLE_OUT_LOW);
	dom_add(d, PIN_CAN_SDO, ROLE_IN);
	dom_add(d, PIN_CAN_CS,  ROLE_IN);      /* 10K pull-up on the CAN rail */
	dom_add(d, PIN_CAN_INT, ROLE_IN);      /* 10K pull-up on the CAN rail */
}

static void dom_add_kline_pins(struct domain *d)
{
	dom_add(d, PIN_K1_TX,   ROLE_IN);      /* board/shifter pull-ups idle high */
	dom_add(d, PIN_K1_RX,   ROLE_IN);
	dom_add(d, PIN_L_SEND,  ROLE_OUT_LOW); /* gates the L pulldown FET */
	dom_add(d, PIN_L_RECV,  ROLE_IN);
	dom_add(d, PIN_K_SLEEP, ROLE_OUT_LOW); /* TJA1027 stays asleep until used */
}

int hw_domain_init(void)
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	 * internal pull-up, and the UARTE drives the pin once the driver opens
	 * it, which is after the rail is up. */
	if (IS_ENABLED(CONFIG_APP_BOARD_HAS_EXT_GNSS)) {
		dom_add(aux, PIN_GNSS_TX,        ROLE_IN);
		dom_add(aux, PIN_GNSS_RX,        ROLE_IN);
		dom_add(aux, PIN_GNSS_TIMEPULSE, ROLE_IN);
	}

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	 * APP_GNSS_BACKUP_OFF_UTC_HOUR if that is set, and comes back with the
	 * receiver's rail: it is what lets the receiver hot-start
	 * (APP_GNSS_BACKUP_SUPPLY). */
	if (IS_ENABLED(CONFIG_APP_BOARD_HAS_EXT_GNSS) && PIN_GNSS_BCKP_EN >= 0) {
		/* Up from boot; a server that wants it dropped says so in its
		 * first reply (hw_gnss_backup_want()). */
		s_bckp_on = IS_ENABLED(CONFIG_APP_GNSS_BACKUP_SUPPLY);
		gpio_pin_configure(hw_gpio0, PIN_GNSS_BCKP_EN,
				   s_bckp_on ? GPIO_OUTPUT_HIGH : GPIO_OUTPUT_LOW);
		/* Not noted: coming up is not a change, and the server holds the
		 * state.  A note here read as "it is on" and overrode a server
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
		dom_rail_sense(aux, PIN_GPS_RAIL_ST,  false,   GPS_RAIL_NAME,
			       true);
		dom_rail_sense(can, PIN_CAN_RAIL_ST,  false,   "PP3V3_CAN",
			       has_can);
		dom_rail_sense(k,   PIN_K3V3_RAIL_ST, false,   "PP3V3_K",
			       has_k);
		dom_rail_sense(k,   PIN_K12V_RAIL_ST, inv_12v, "PP12V_K",
			       has_k);
	}

	/* AIO inputs (v2.1): external 100K/10K dividers define the level. */
	static const int8_t aio[] = { PIN_AIO1, PIN_AIO2, PIN_AIO3,
				      PIN_AIO4, PIN_AIO5, PIN_AIO6 };
	for (int i = 0; i < (int)ARRAY_SIZE(aio); i++) {
		if (aio[i] >= 0) {
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	bool was_on = s_bckp_on;
	bool was_hold = s_bckp_hold;

	if (!IS_ENABLED(CONFIG_APP_GNSS_BACKUP_SUPPLY) || PIN_GNSS_BCKP_EN < 0) {
		return false;
	}
	s_bckp_hold = !on;
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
